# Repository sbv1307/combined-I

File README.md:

# Combind projects: Energimåling, autoStart og ProgrammablePulsGenerator

The purpose of this project is to assemble PCB manufacturing at the same PDB for the three projects.

Only information and data explicit required for this process will be collected here.

Informatino and data related the the individual projects will be found in their onwn projects. E.g. There will be not software / firmware in this project.

Project Version history:
 * V0.0.1 - Initial commit. Project structure, submodule and Page settings.
 * V0.0.2 - Local KiCad Libraries added
 * V1.0.0 - Schematics and components placed on BCB for Energimåling added to the project.
 * V2.0.0 - Schematics and components placed on BCB for autoStart added to the project.
 * V.0.0 - Schematics and components placed on BCB for ProgrameablePulseGenerator added to the project.<br>
For this version (3.0.0) all KiCad Local libraries in the submodule were updated:<br>
All [JLCPCB](https://jlcpcb.com/) extended components and all non [JLCPCB](https://jlcpcb.com/) components were update wit the option "Exclude from BO M list.<br>
Further som footprints were modified and fixed for errors.<br>
Several components is all schmatics were replaced with the new modified ones.
 * V3.0.1 - Feature update - Adding critical traces by hand and prepare for autorouter to do the rest.
 * V3.1.0 - Feature update - From V3.0.0: Aoto routed and ctitical tracks modified afterwards.
 * V3.1.1 - Feature update - GND zone filled for Energimåling
 * V3.1.2 - Feature update - GND zone filled for Arduino USB-Serial card.
 * V3.1.3 - Feature update - GND zone filled for autostart og ProgrammablePulsGenerator.

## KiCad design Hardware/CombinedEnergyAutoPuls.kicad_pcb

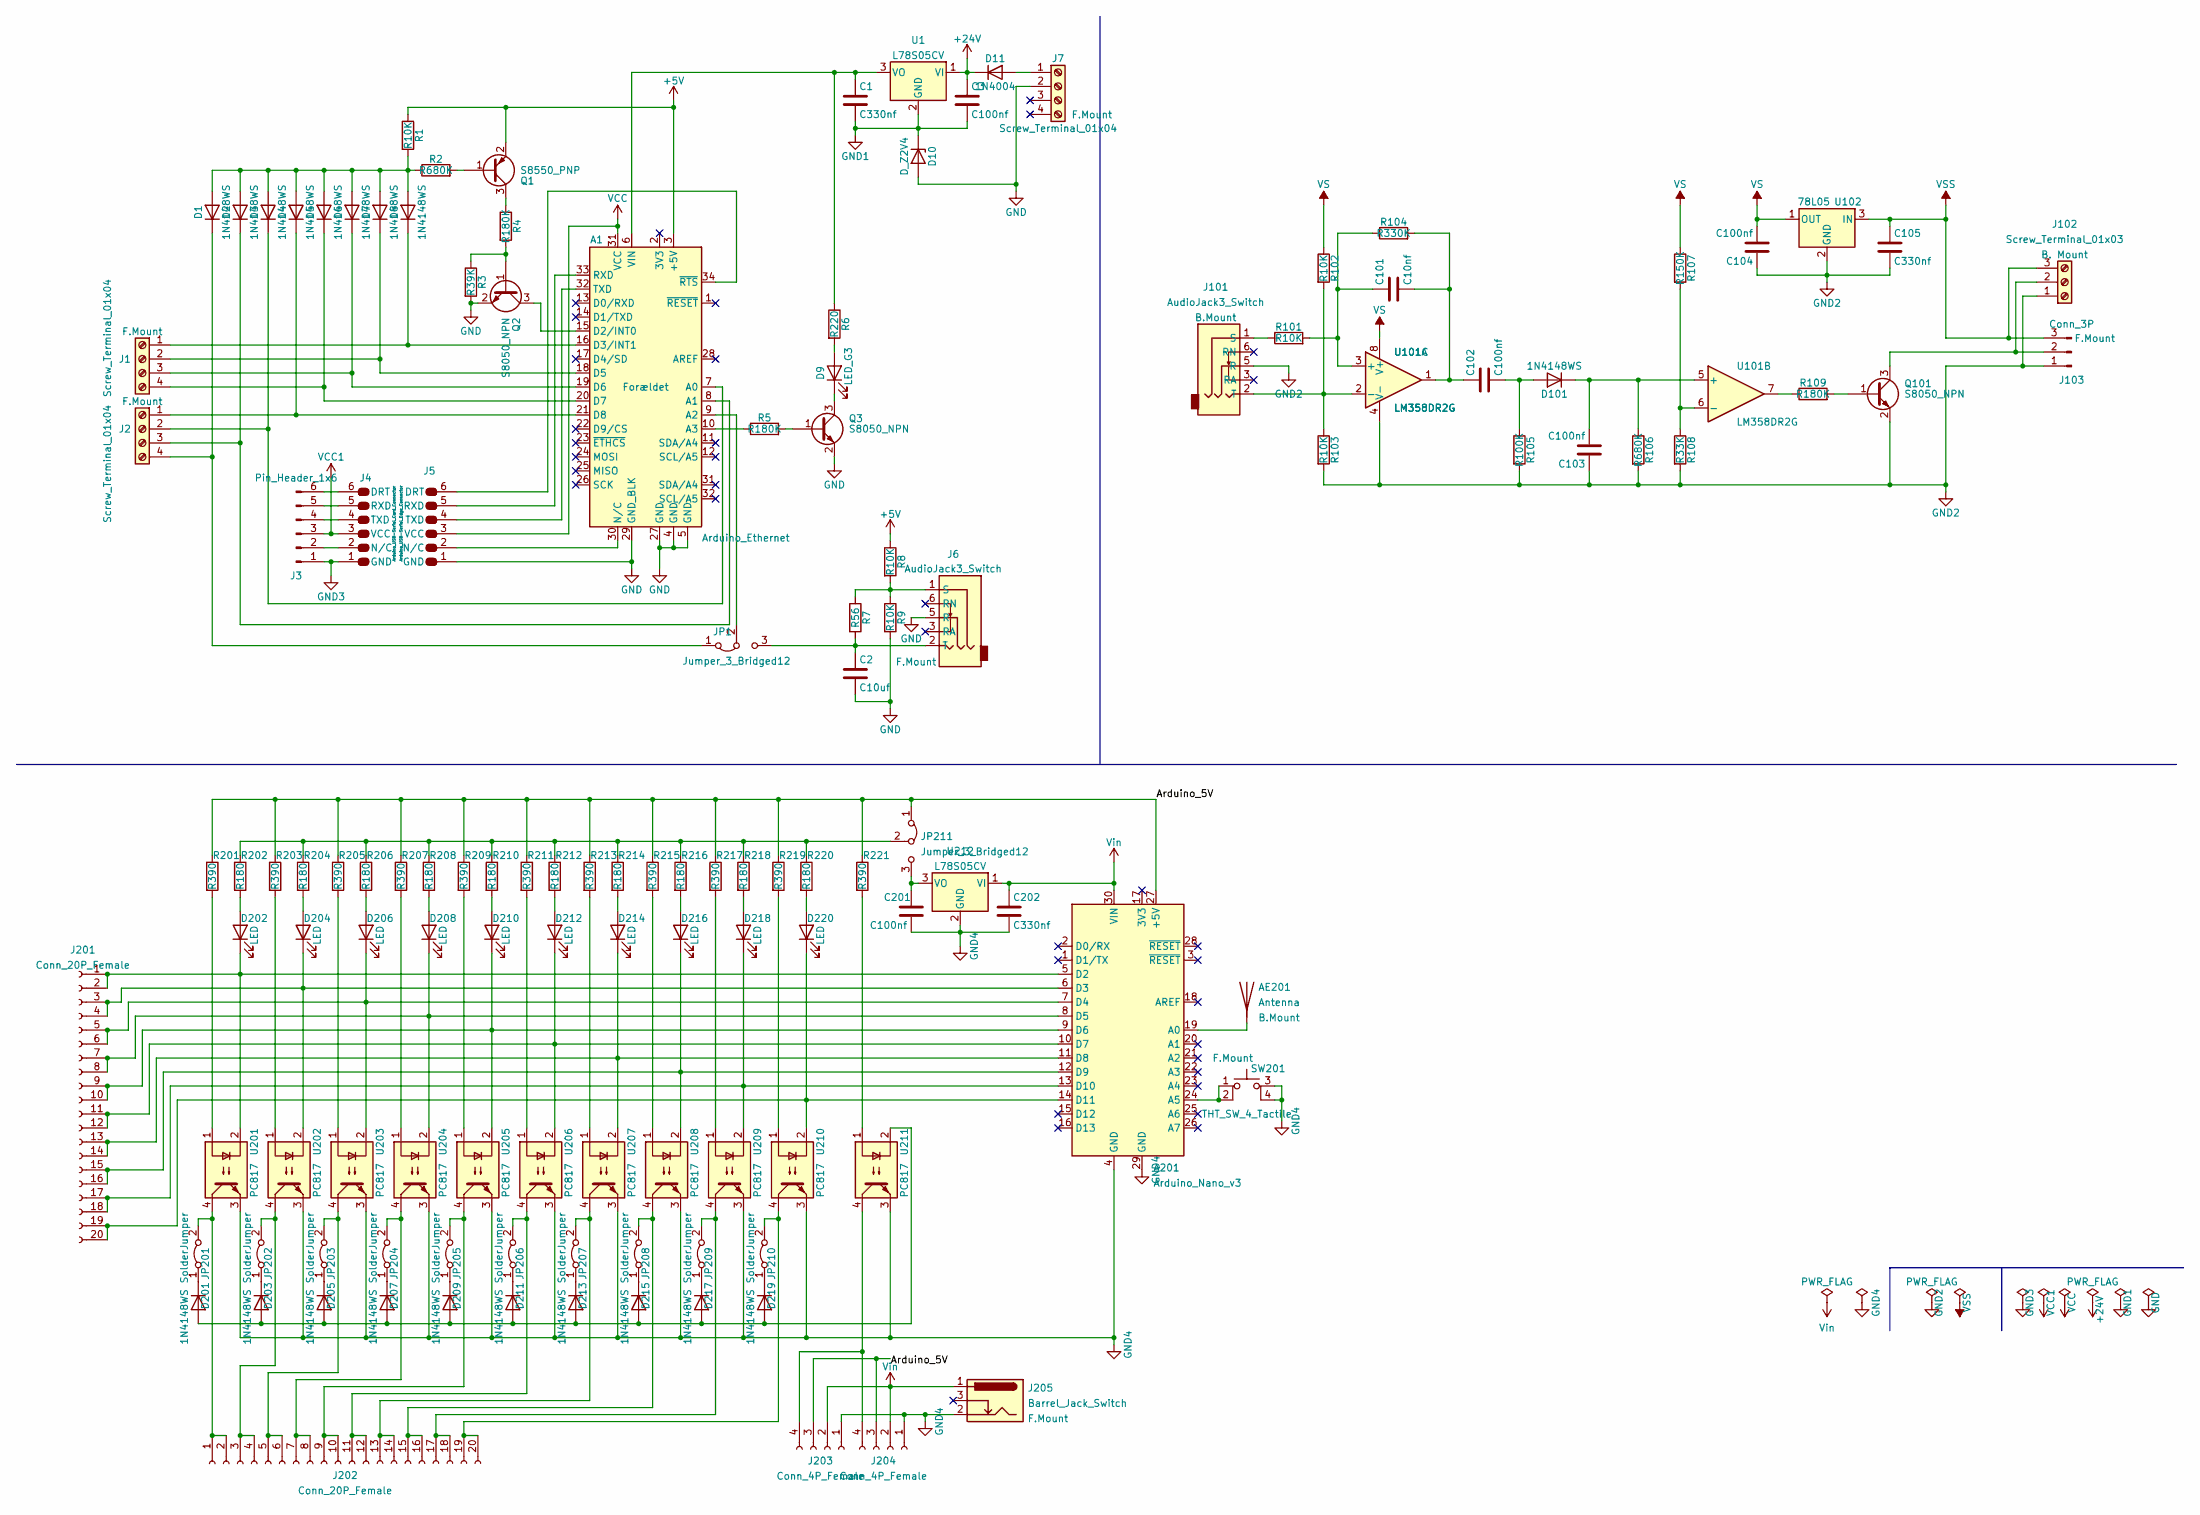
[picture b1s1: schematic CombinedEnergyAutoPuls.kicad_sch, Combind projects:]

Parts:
A1: Arduino_Ethernet; Arduino_Ethernet_WithMountingHoles; MFR. Part # A000061; Digi-Key Part # 1050-1043-ND
A201: Arduino_Nano_v3; Arduino_Nano; MFR. Part # A000005; Digi-Key Part # 1050-1001-ND
AE201: Antenna; Undefined_Antenna(B.Mount)
C1, C105, C202: C330nf; C_0805_2012Metric; MFR. Part # 0805B334K500NT; JLCPCB Part # C1740
C2: C10uf; C_0603_1608Metric; MFR. Part # CL10A106KP8NNNC; JLCPCB Part # C19702
C3, C102, C103, C104, C201: C100nf; C_0402_1005Metric; MFR. Part # CL05B104KO5NNNC; JLCPCB Part # C1525
C101: C10nf; C_0402_1005Metric; MFR. Part # CL05B103KB5NNNC; JLCPCB Part # C15195
D1, D2, D3, D4, D5, D6, D7, D8, D101, D201, D203, D205, D207, D209, D211, D213, D215, D217, D219: 1N4148WS; D_SOD-323F; MFR. Part # 1N4148WS; JLCPCB Part # C2128
D9: LED_G3; LED_D3.0mm; MFR. Part # 151031VS04000; Digi-Key Part # 732-5007-ND
D10: D_Z2V4; D_DO-35_SOD27_P7.62mm_Horizontal; MFR. Part # BZX55C2V4; JLCPCB Part # C2504
D11: 1N4004; D_DO-41_SOD81_P12.70mm_Horizontal; MFR. Part # 1N4004; JLCPCB Part # C3058
D202, D204, D206, D208, D210, D212, D214, D216, D218, D220: LED; LED_0805_2012Metric; MFR. Part # NCD0805R1; JLCPCB Part # C84256
J1, J2, J7: Screw_Terminal_01x04; TerminalBlock_PT-1,5-4-5.0-H_1x04_P5.00mm_Horizontal-(F.Mou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; MFR. Part # 950-T-DS/02; Digi-Key Part # 3072-950-T-DS/02-ND
J3: Pin_Header_1x6; PinHeader_1x06_P_0,1in_Vertical; MFR. Part # C37208; JLCPCB Part # C37208
J4: Arduino_USB-Serial_Card_Connector; Arduino_USB-Serial_Card
J5: Arduino_USB-Serial_Edge_Connector; Arduino_USB-Serial_Card_EdgeConn
J6: AudioJack3_Switch; AUDIO_JACK_ASJ-195-L-HT-(F.Mount); MFR. Part # ASJ-195-L-HT; Digi-Key Part # 2057-ASJ-195-L-HT-ND
J101: AudioJack3_Switch; AUDIO_JACK_ASJ-195-L-HT-(B.Mount); MFR. Part # ASJ-195-L-HT; Digi-Key Part # 2057-ASJ-195-L-HT-ND
J102: Screw_Terminal_01x03; Phoenix_TERM_BLOCK_3POS_45DEG_5MM_PCB-(B.Mount); MFR. Part # 1988817; Digi-Key Part # 277-1765-ND
J103: Conn_3P; PinHeader_1x03_P_5mm_Vertical-(F.Mount)
J201, J202: Conn_20P_Female; PinHeader_1x20_P2.54mm_Vertical; MFR. Part # 4155; Digi-Key Part # 1528-2927-ND
J203, J204: Conn_4P_Female; PinHeader_1x04_P2.54mm_Vertical; MFR. Part # 4155; Digi-Key Part # 1528-2927-ND
J205: Barrel_Jack_Switch; BarrelJack_Horizontal(F.Mount); MFR. Part # PJ-058AH; Digi-Key Part # CP-058AH-ND
JP1, JP211: Jumper_3_Bridged12; PinHeader_1x03_P2.54mm_Vertical
JP201, JP202, JP203, JP204, JP205, JP206, JP207, JP208, JP209, JP210: SolderJumper; SolderJumper-2_P1.3mm_Bridged_RoundedPad1.0x1.5mm(B.Mount)
Q1: S8550_PNP; SOT-23; MFR. Part # S8550; JLCPCB Part # C105432
Q2, Q3, Q101: S8050_NPN; SOT-23; MFR. Part # SS8050; JLCPCB Part # C2150
R1, R8, R9, R101, R102, R103: R10K; R_0402_1005Metric; MFR. Part # 0402WGF1002TCE; JLCPCB Part # C25744
R2, R106: R680K; R_0603_1608Metric; MFR. Part # 0603WAF6803T5E; JLCPCB Part # C25822
R3: R39K; R_0402_1005Metric; MFR. Part # 0402WGF3902TCE; JLCPCB Part # C25783
R4, R5, R109: R180K; R_0603_1608Metric; MFR. Part # 0603WAF1803T5E; JLCPCB Part # C22827
R6: R220; R_0805_2012Metric; MFR. Part # 0805W8F2200T5E; JLCPCB Part # C17557
R7: R56; R_1206_3216Metric; MFR. Part # 1206W4F1003T5E; JLCPCB Part # C17900
R104: R330K; R_0402_1005Metric; MFR. Part # 0402WGF3303TCE; JLCPCB Part # C25778
R105: R100K; R_0402_1005Metric; MFR. Part # 0402WGF1003TCE; JLCPCB Part # C25741
R107: R150K; R_0402_1005Metric; MFR. Part # 0402WGF1503TCE; JLCPCB Part # C25755
R108: R33K; R_0402_1005Metric; MFR. Part # 0402WGF3302TCE; JLCPCB Part # C25779
R201, R203, R205, R207, R209, R211, R213, R215, R217, R219, R221: R390; R_0603_1608Metric; MFR. Part # 0603WAF3900T5E; JLCPCB Part # C23151
R202, R204, R206, R208, R210, R212, R214, R216, R218, R220: R180; R_0805_2012Metric; MFR. Part # 0805W8F1800T5E; JLCPCB Part # C25270
SW201: THT_SW_4_Tactile; THT_SW_Tactile(F.Mount)
U1, U212: L78S05CV; TO-220-3_Vertical; MFR. Part # L78S05CV; Digi-Key Part # 497-1468-5-ND
U101: LM358DR2G; SOIC-8_3.9x4.9mm_P1.27mm; MFR. Part # LM358DR2G; JLCPCB Part # C7950
U102: 78L05; SOT-89-3; MFR. Part # 78L05G-AB3-R; JLCPCB Part # C71136
U201, U202, U203, U204, U205, U206, U207, U208, U209, U210, U211: PC817; DIP-4_W7.62mm_Slim(F.Mount)

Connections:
+5V: A1.3 (+5V), Q1.2 (E), R1.1, R8.1
+24V: C3.1, D11.1 (K), U1.1 (VI)
/Arduino_5V: A201.27 (+5V), JP211.1 (A), R201.1, R203.1, R205.1, R207.1, R209.1, R211.1, R213.1, R215.1, R217.1, R219.1, R221.1
GND: A1.4 (GND), A1.5 (GND), A1.27 (GND), A1.29 (GND_BLK), C2.2, D10.2 (A), J5.1 (GND), J6.5 (R), J7.2, Q2.2 (E), Q3.2 (E), R3.2, R9.2
GND1: C1.2, C3.2, D10.1 (K), U1.2 (GND)
GND2: C103.1, C104.1, C105.2, J101.5 (R), J102.1, J103.1, Q101.2 (E), R103.2, R105.2, R106.2, R108.2, U101.4 (V-), U102.2 (GND)
GND3: J3.1, J4.1 (GND)
GND4: A201.4 (GND), A201.29 (GND), C201.2, C202.2, J203.1, J204.1, J205.2, SW201.3 (K), SW201.4 (A), U201.3, U202.3, U203.3, U204.3, U205.3, U206.3, U207.3, U208.3, U209.3, U210.3, U211.3, U212.2 (GND)
unnamed: A1.6 (VIN), C1.1, R6.1, U1.3 (VO)
unnamed: A1.7 (A0), D3.1 (K), J2.2
unnamed: A1.8 (A1), D2.1 (K), J2.3
unnamed: A1.9 (A2), JP1.2 (C)
unnamed: A1.10 (A3), R5.1
unnamed: A1.15 (D2/INT0), Q2.3 (C)
unnamed: A1.16 (D3/INT1), D8.1 (K), J1.1
unnamed: A1.18 (D5), D7.1 (K), J1.2
unnamed: A1.19 (D6), D6.1 (K), J1.3
unnamed: A1.20 (D7), D5.1 (K), J1.4
unnamed: A1.21 (D8), D4.1 (K), J2.1
unnamed: A1.30 (N/C), J5.2 (N/C)
unnamed: A1.32 (TXD), J5.4 (TXD)
unnamed: A1.33 (RXD), J5.5 (RXD)
unnamed: A1.34 (~RTS), J5.6 (DRT)
unnamed: A201.5 (D2), D202.1 (K), J201.1, J201.2, U201.2
unnamed: A201.6 (D3), D204.1 (K), J201.3, J201.4, U202.2
unnamed: A201.7 (D4), D206.1 (K), J201.5, J201.6, U203.2
unnamed: A201.8 (D5), D208.1 (K), J201.7, J201.8, U204.2
unnamed: A201.9 (D6), D210.1 (K), J201.9, J201.10, U205.2
unnamed: A201.10 (D7), D212.1 (K), J201.11, J201.12, U206.2
unnamed: A201.11 (D8), D214.1 (K), J201.13, J201.14, U207.2
unnamed: A201.12 (D9), D216.1 (K), J201.15, J201.16, U208.2
unnamed: A201.13 (D10), D218.1 (K), J201.17, J201.18, U209.2
unnamed: A201.14 (D11), D220.1 (K), J201.19, J201.20, U210.2
unnamed: A201.19 (A0), AE201.1 (A)
unnamed: A201.24 (A5), SW201.1, SW201.2
unnamed: C2.1, J6.2 (T), JP1.3 (B), R7.2
unnamed: C101.1, R101.2, R104.1, U101.3 (+)
unnamed: C101.2, C102.1, R104.2, U101.1
unnamed: C102.2, D101.2 (A), R105.1
unnamed: C103.2, D101.1 (K), R106.1, U101.5 (+)
unnamed: C201.1, JP211.3 (B), U212.3 (VO)
unnamed: D1.1 (K), J2.4, JP1.1 (A)
unnamed: D1.2 (A), D2.2 (A), D3.2 (A), D4.2 (A), D5.2 (A), D6.2 (A), D7.2 (A), D8.2 (A), R1.2, R2.1
unnamed: D9.1 (K), Q3.3 (C)
unnamed: D9.2 (A), R6.2
unnamed: D11.2 (A), J7.1
unnamed: D201.1 (K), JP201.1 (A)
unnamed: D201.2 (A), D203.2 (A), D205.2 (A), D207.2 (A), D209.2 (A), D211.2 (A), D213.2 (A), D215.2 (A), D217.2 (A), D219.2 (A), U211.2
unnamed: D202.2 (A), R202.2
unnamed: D203.1 (K), JP202.1 (A)
unnamed: D204.2 (A), R204.2
unnamed: D205.1 (K), JP203.1 (A)
unnamed 52: D206.2 (A), R206.2; also elsewhere on the board
unnamed: D207.1 (K), JP204.1 (A)
unnamed: D208.2 (A), R208.2
unnamed: D209.1 (K), JP205.1 (A)
unnamed: D210.2 (A), R210.2
unnamed: D211.1 (K), JP206.1 (A)
unnamed: D212.2 (A), R212.2
unnamed: D213.1 (K), JP207.1 (A)
unnamed: D214.2 (A), R214.2
unnamed: D215.1 (K), JP208.1 (A)
unnamed: D216.2 (A), R216.2
unnamed: D217.1 (K), JP209.1 (A)
unnamed: D218.2 (A), R218.2
unnamed: D219.1 (K), JP210.1 (A)
unnamed: D220.2 (A), R220.2
unnamed: J3.2, J4.2 (N/C)
unnamed: J3.4, J4.4 (TXD)
unnamed: J3.5, J4.5 (RXD)
unnamed: J3.6, J4.6 (DRT)
unnamed: J6.1 (S), R7.1, R8.2, R9.1
unnamed: J101.1 (S), R101.1
unnamed: J101.2 (T), R102.2, R103.1, U101.2 (-)
unnamed: J102.2, J103.2, Q101.3 (C)
unnamed: J202.1, J202.2, JP201.2 (B), U201.4
unnamed: J202.3, J202.4, JP202.2 (B), U202.4
unnamed: J202.5, J202.6, JP203.2 (B), U203.4
unnamed: J202.7, J202.8, JP204.2 (B), U204.4
unnamed: J202.9, J202.10, JP205.2 (B), U205.4
unnamed: J202.11, J202.12, JP206.2 (B), U206.4
unnamed: J202.13, J202.14, JP207.2 (B), U207.4
unnamed: J202.15, J202.16, JP208.2 (B), U208.4
unnamed: J202.17, J202.18, JP209.2 (B), U209.4
unnamed: J202.19, J202.20, JP210.2 (B), U210.4
unnamed: J203.3, J204.3
unnamed: J203.4, J204.4, U211.4
unnamed 87: JP211.2 (C), R202.1, R204.1, R206.1, R208.1, R210.1, R212.1, R214.1, R216.1, R218.1, R220.1; also elsewhere on the board
unnamed: Q1.1 (B), R2.2
unnamed: Q1.3 (C), R4.1
unnamed: Q2.1 (B), R3.1, R4.2
unnamed: Q3.1 (B), R5.2
unnamed: Q101.1 (B), R109.2
unnamed: R107.2, R108.1, U101.6 (-)
unnamed: R109.1, U101.7
unnamed: R201.2, U201.1
unnamed: R203.2, U202.1
unnamed: R205.2, U203.1
unnamed: R207.2, U204.1
unnamed: R209.2, U205.1
unnamed: R211.2, U206.1
unnamed: R213.2, U207.1
unnamed: R215.2, U208.1
unnamed: R217.2, U209.1
unnamed: R219.2, U210.1
unnamed: R221.2, U211.1
VCC: A1.31 (VCC), J5.3 (VCC)
VCC1: J3.3, J4.3 (VCC)
VS: C104.2, R102.1, R107.1, U101.8 (V+), U102.1 (OUT)
VSS: C105.1, J102.3, J103.3, U102.3 (IN)
Vin: A201.30 (VIN), C202.1, J203.2, J204.2, J205.1, U212.1 (VI)

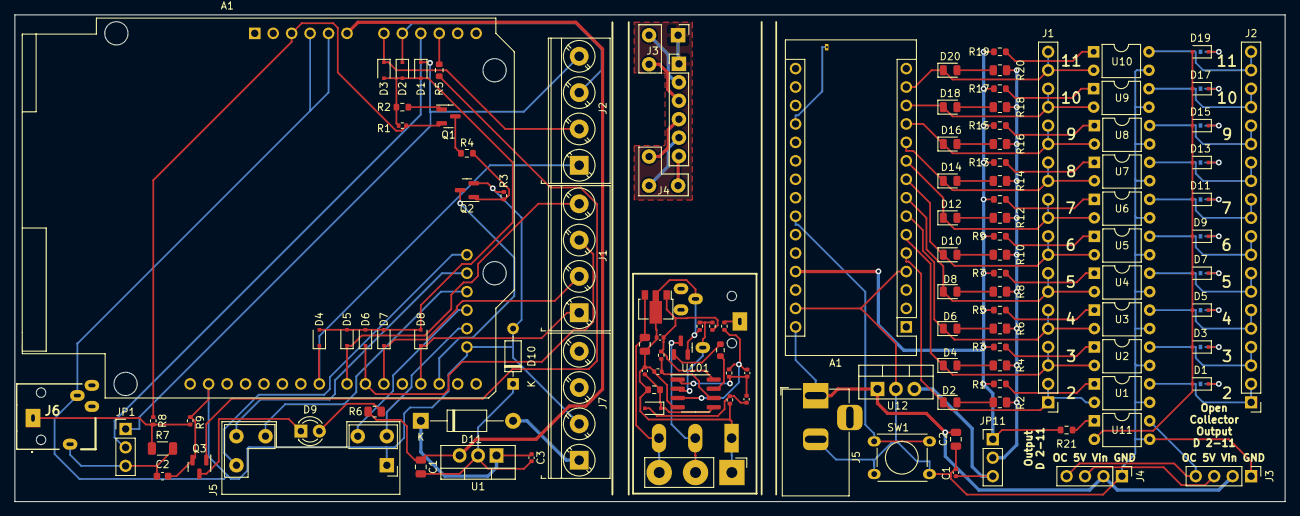
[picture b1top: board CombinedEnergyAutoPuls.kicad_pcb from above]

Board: 2 copper layers, 174.9 x 67.0 mm, 131 parts (0 on the bottom side), 111 nets.

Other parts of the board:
Rw: R180; R_0805_2012Metric

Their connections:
unnamed 52: Rw.2; also elsewhere on the board
unnamed 87: Rw.1; also elsewhere on the board

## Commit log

2022-04-05 Initial commit. Project structure, submodule and Page settings.
2022-04-05 UPD: Local libraries added to main
2022-04-05 Revert "UPD: Local libraries added to main"
    This reverts commit 440ef0d9d3a5a2afac65d7e2dc68a54023e6daa6.
2022-04-05 Local KiCad Libraries added
2022-04-05 STAGE: Schematics finished
2022-04-06 FIX: Fixes made to local libraies
2022-04-06 STAGE: Component placed on PCB
2022-04-07 FEAT: Final commit for branch
2022-04-07 Schematics and components placed on BCB for autoStart added to the project.
2022-04-09 UPD: - Schematics and components placed on BCB for ProgrameablePulseGenerator added to the project
2022-04-10 UPD: Silkmask references modified
2022-04-10 DOC: Final commit before merging branch Pulsgenerator into main
2022-04-10 UPD: Commit changes before merge branch Pulsgenerator
2022-04-10 UPD - Adding critical traces by hand and prepare for autorouter to do the rest.
2022-04-11 PCB Auto routed.
2022-04-12 UPD: minor track changes to PCB
2022-04-12 DOC: README.md updated
2022-04-12 GND zone filled for Energimaaling
2022-04-12 Feature update - GND zone filled for Arduino USB-Serial card.
2022-04-12 Feature update - GND zone filled for autostart og ProgrammablePulsGenerator.
2022-04-12 FIX: Zone copper arias intersect at pulsgenerator
